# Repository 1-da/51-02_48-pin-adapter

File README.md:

This is the Adapter to connect 360-Clip TSOP-48 Nand Reader to the FlashcatUSB XPORT programmer designed with KiCAD 5.1.9.

Please notice that the adapter supports only TSOP-48 NAND flash (TSOP-56 is not supported)

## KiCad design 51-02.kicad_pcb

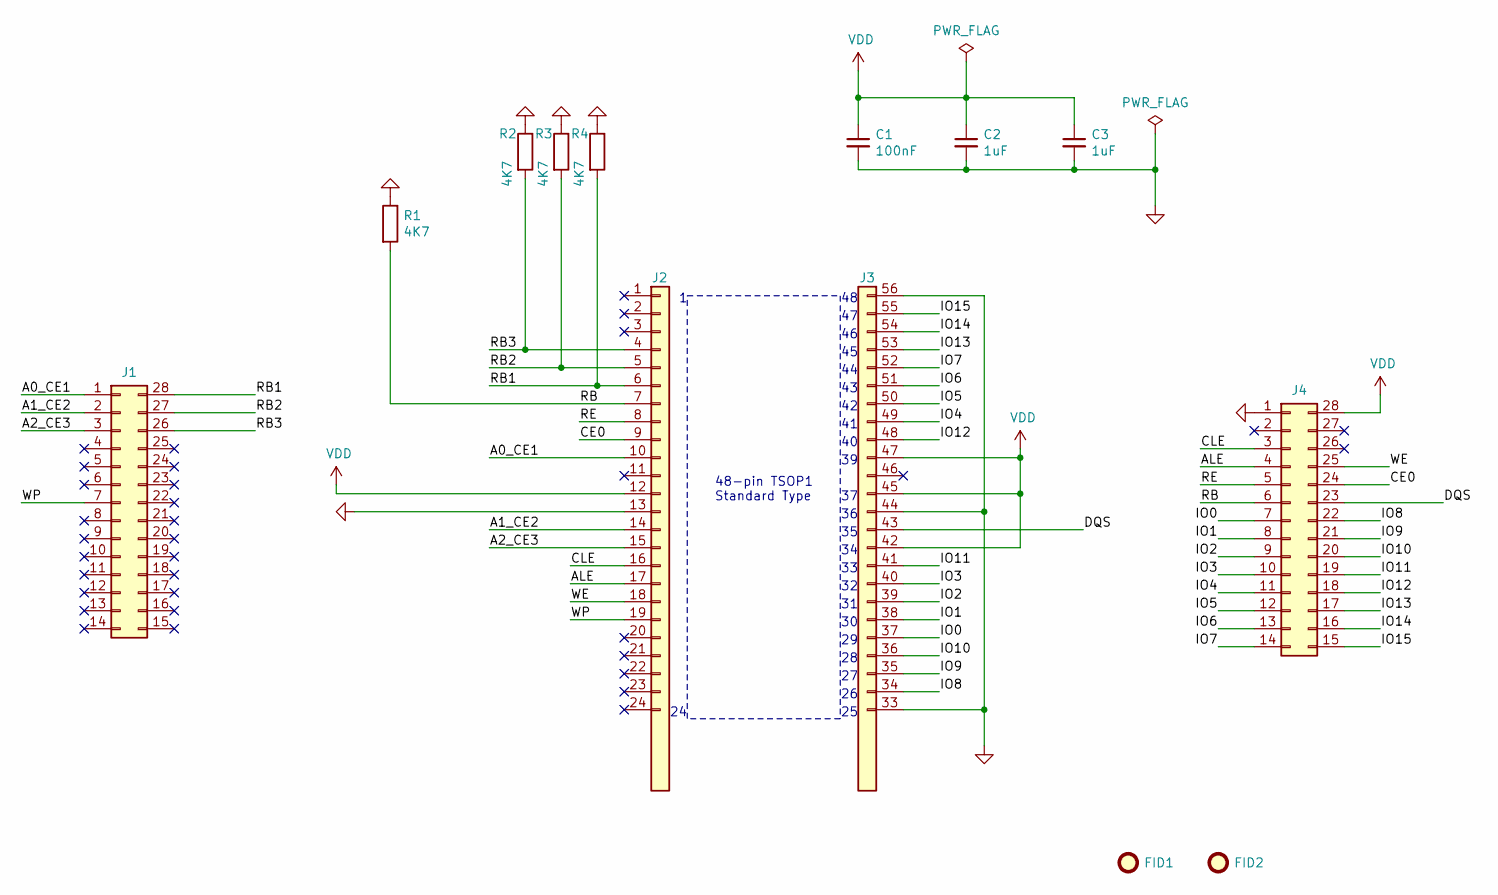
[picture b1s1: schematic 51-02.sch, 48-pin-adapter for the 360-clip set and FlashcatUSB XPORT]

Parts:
C1: 100nF; C_0805_vtech-snom; Tolerance 20%; Rating 50V; PART NUMBER 22-XXXX
C2, C3: 1uF; C_0805_vtech-snom; Tolerance 20%; Rating 50V; PART NUMBER 22-XXXX
FID1, FID2: Fiducial; 1-DA_Fiducial_1.5mm_Mask3mm
J1, J4: 1_DA_Conn_02x14_Counter_Clockwise; 1-DA_PinHeader_2x14_P2.00mm_Vertical
J2: Conn_01x24_I; 1-DA_PinHeader_I_1x24_P2.54mm_Vertical
J3: Conn_01x24_II; 1-DA_PinHeader_II_1x24_P2.54mm_Vertical
R1, R2, R3, R4: 4K7; R_0805_vtech-snom; Tolerance 5%; Rating 1/10 W; PART NUMBER XX-XXXX

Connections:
/A0_CE1: J1.1, J2.10
/A1_CE2: J1.2, J2.14
/A2_CE3: J1.3, J2.15
/ALE: J2.17, J4.4
/CE0: J2.9, J4.24
/CLE: J2.16, J4.3
/DQS: J3.43, J4.23
/IO0: J3.37, J4.7
/IO1: J3.38, J4.8
/IO2: J3.39, J4.9
/IO3: J3.40, J4.10
/IO4: J3.49, J4.11
/IO5: J3.50, J4.12
/IO6: J3.51, J4.13
/IO7: J3.52, J4.14
/IO8: J3.34, J4.22
/IO9: J3.35, J4.21
/IO10: J3.36, J4.20
/IO11: J3.41, J4.19
/IO12: J3.48, J4.18
/IO13: J3.53, J4.17
/IO14: J3.54, J4.16
/IO15: J3.55, J4.15
/RB: J2.7, J4.6, R1.2
/RB1: J1.28, J2.6, R4.2
/RB2: J1.27, J2.5, R3.2
/RB3: J1.26, J2.4, R2.2
/RE: J2.8, J4.5
/WE: J2.18, J4.25
/WP: J1.7, J2.19
GND: C1.2, C2.2, C3.2, J2.13, J3.33, J3.44, J3.56, J4.1, R1.1, R2.1, R3.1, R4.1
VDD: C1.1, C2.1, C3.1, J2.12, J3.42, J3.45, J3.47, J4.28

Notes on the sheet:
48-pin TSOP1 Standard Type

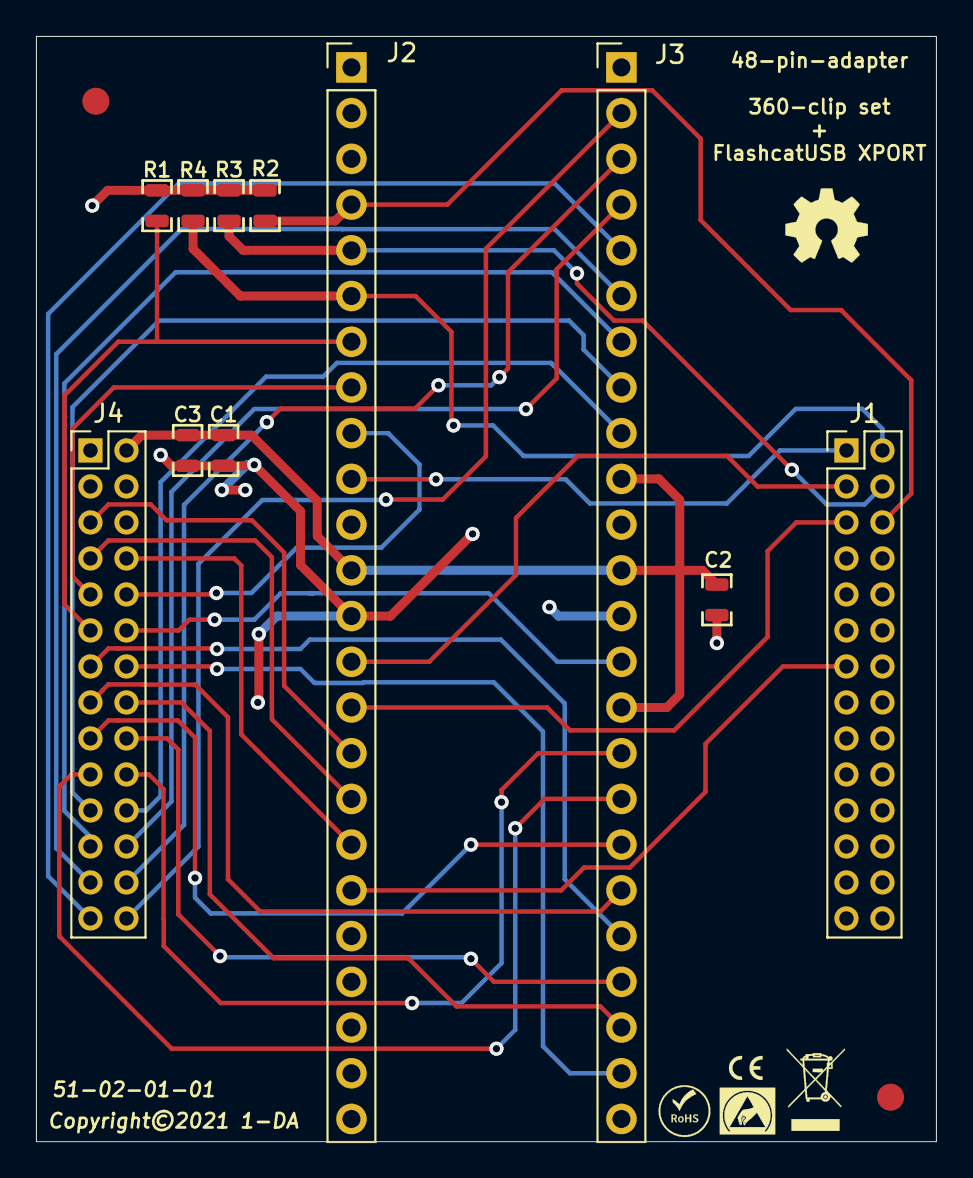
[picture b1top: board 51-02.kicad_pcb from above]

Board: 2 copper layers, 50.0 x 61.4 mm, 13 parts (0 on the bottom side), 32 nets.

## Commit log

2021-04-04 first touch
2021-04-05 sch first release
2021-04-06 2x14 2mm raster
2021-04-08 first net generarted
2021-04-11 first complete release
2021-04-11 silk+3d
2021-04-12 plot gerber files

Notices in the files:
51-02.kicad_pcb:
Copyright©2021 1-DA
